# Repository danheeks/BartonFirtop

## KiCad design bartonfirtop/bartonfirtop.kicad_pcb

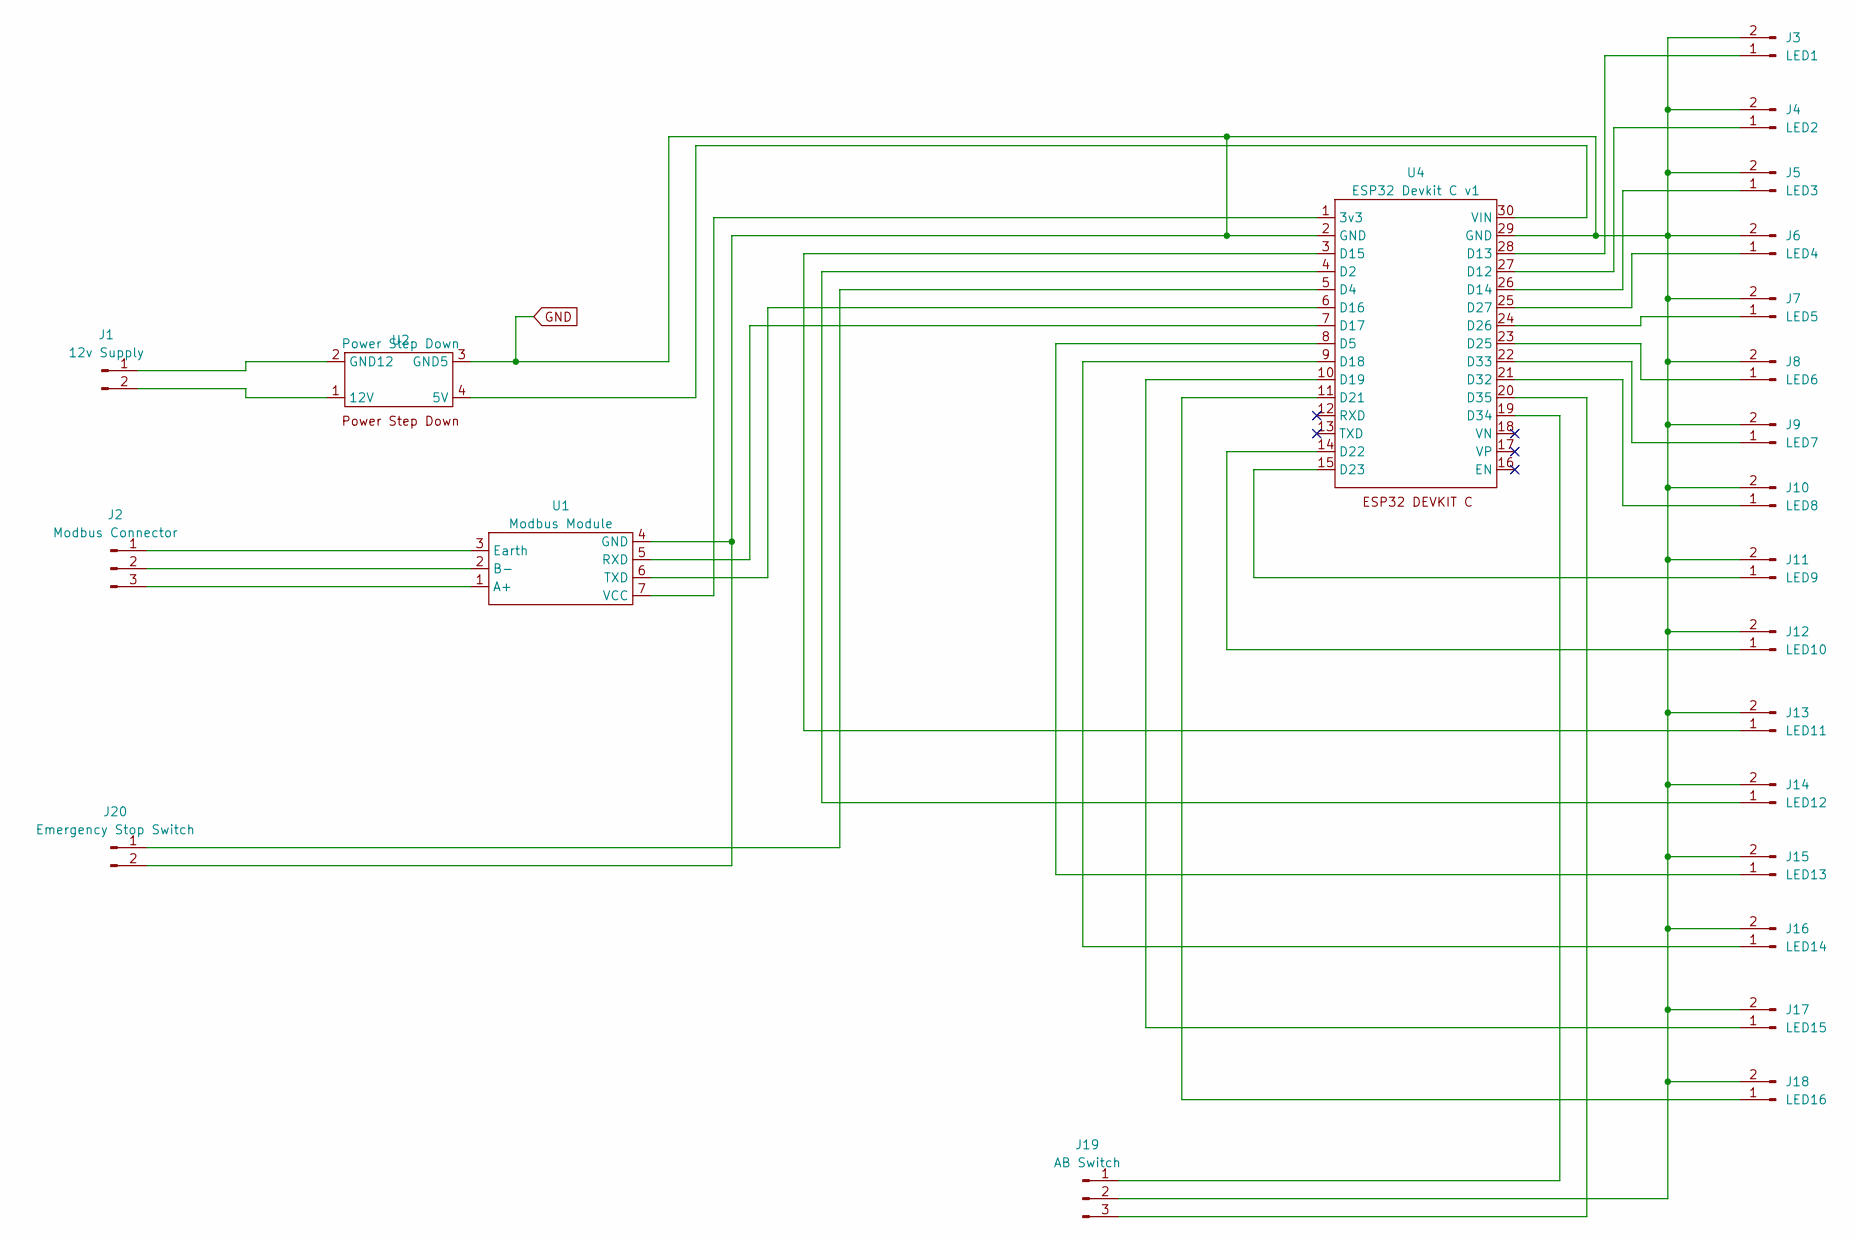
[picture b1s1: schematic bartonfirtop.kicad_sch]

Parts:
J1: 12v Supply; Molex_KK-254_AE-6410-02A_1x02_P2.54mm_Vertical
J2: Modbus Connector; Molex_KK-254_AE-6410-03A_1x03_P2.54mm_Vertical
J3: LED1; Molex_KK-254_AE-6410-02A_1x02_P2.54mm_Vertical
J4: LED2; Molex_KK-254_AE-6410-02A_1x02_P2.54mm_Vertical
J5: LED3; Molex_KK-254_AE-6410-02A_1x02_P2.54mm_Vertical
J6: LED4; Molex_KK-254_AE-6410-02A_1x02_P2.54mm_Vertical
J7: LED5; Molex_KK-254_AE-6410-02A_1x02_P2.54mm_Vertical
J8: LED6; Molex_KK-254_AE-6410-02A_1x02_P2.54mm_Vertical
J9: LED7; Molex_KK-254_AE-6410-02A_1x02_P2.54mm_Vertical
J10: LED8; Molex_KK-254_AE-6410-02A_1x02_P2.54mm_Vertical
J11: LED9; Molex_KK-254_AE-6410-02A_1x02_P2.54mm_Vertical
J12: LED10; Molex_KK-254_AE-6410-02A_1x02_P2.54mm_Vertical
J13: LED11; Molex_KK-254_AE-6410-02A_1x02_P2.54mm_Vertical
J14: LED12; Molex_KK-254_AE-6410-02A_1x02_P2.54mm_Vertical
J15: LED13; Molex_KK-254_AE-6410-02A_1x02_P2.54mm_Vertical
J16: LED14; Molex_KK-254_AE-6410-02A_1x02_P2.54mm_Vertical
J17: LED15; Molex_KK-254_AE-6410-02A_1x02_P2.54mm_Vertical
J18: LED16; Molex_KK-254_AE-6410-02A_1x02_P2.54mm_Vertical
J19: AB Switch; Molex_KK-254_AE-6410-03A_1x03_P2.54mm_Vertical
J20: Emergency Stop Switch; Molex_KK-254_AE-6410-02A_1x02_P2.54mm_Vertical
U1: Modbus Module
U2: Power Step Down; Step Down Buck Converter 24V - 5V
U4: ESP32 Devkit C v1; MODULE_ESP32_DEVKIT_V1

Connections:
GND: J3.2, J4.2, J5.2, J6.2, J7.2, J8.2, J9.2, J10.2, J11.2, J12.2, J13.2, J14.2, J15.2, J16.2, J17.2, J18.2, J19.2, J20.2, U1.4 (GND), U2.3 (GND5), U4.2 (GND), U4.29 (GND)
unnamed: J1.1, U2.2 (GND12)
unnamed: J1.2, U2.1 (12V)
unnamed: J2.1, U1.3 (Earth)
unnamed: J2.2, U1.2 (B-)
unnamed: J2.3, U1.1 (A+)
unnamed: J3.1, U4.28 (D13)
unnamed: J4.1, U4.27 (D12)
unnamed: J5.1, U4.26 (D14)
unnamed: J6.1, U4.25 (D27)
unnamed: J7.1, U4.24 (D26)
unnamed: J8.1, U4.23 (D25)
unnamed: J9.1, U4.22 (D33)
unnamed: J10.1, U4.21 (D32)
unnamed: J11.1, U4.15 (D23)
unnamed: J12.1, U4.14 (D22)
unnamed: J13.1, U4.3 (D15)
unnamed: J14.1, U4.4 (D2)
unnamed: J15.1, U4.8 (D5)
unnamed: J16.1, U4.9 (D18)
unnamed: J17.1, U4.10 (D19)
unnamed: J18.1, U4.11 (D21)
unnamed: J19.1, U4.19 (D34)
unnamed: J19.3, U4.20 (D35)
unnamed: J20.1, U4.5 (D4)
unnamed: U1.5 (RXD), U4.7 (D17)
unnamed: U1.6 (TXD), U4.6 (D16)
unnamed: U1.7 (VCC), U4.1 (3v3)
unnamed: U2.4 (5V), U4.30 (VIN)

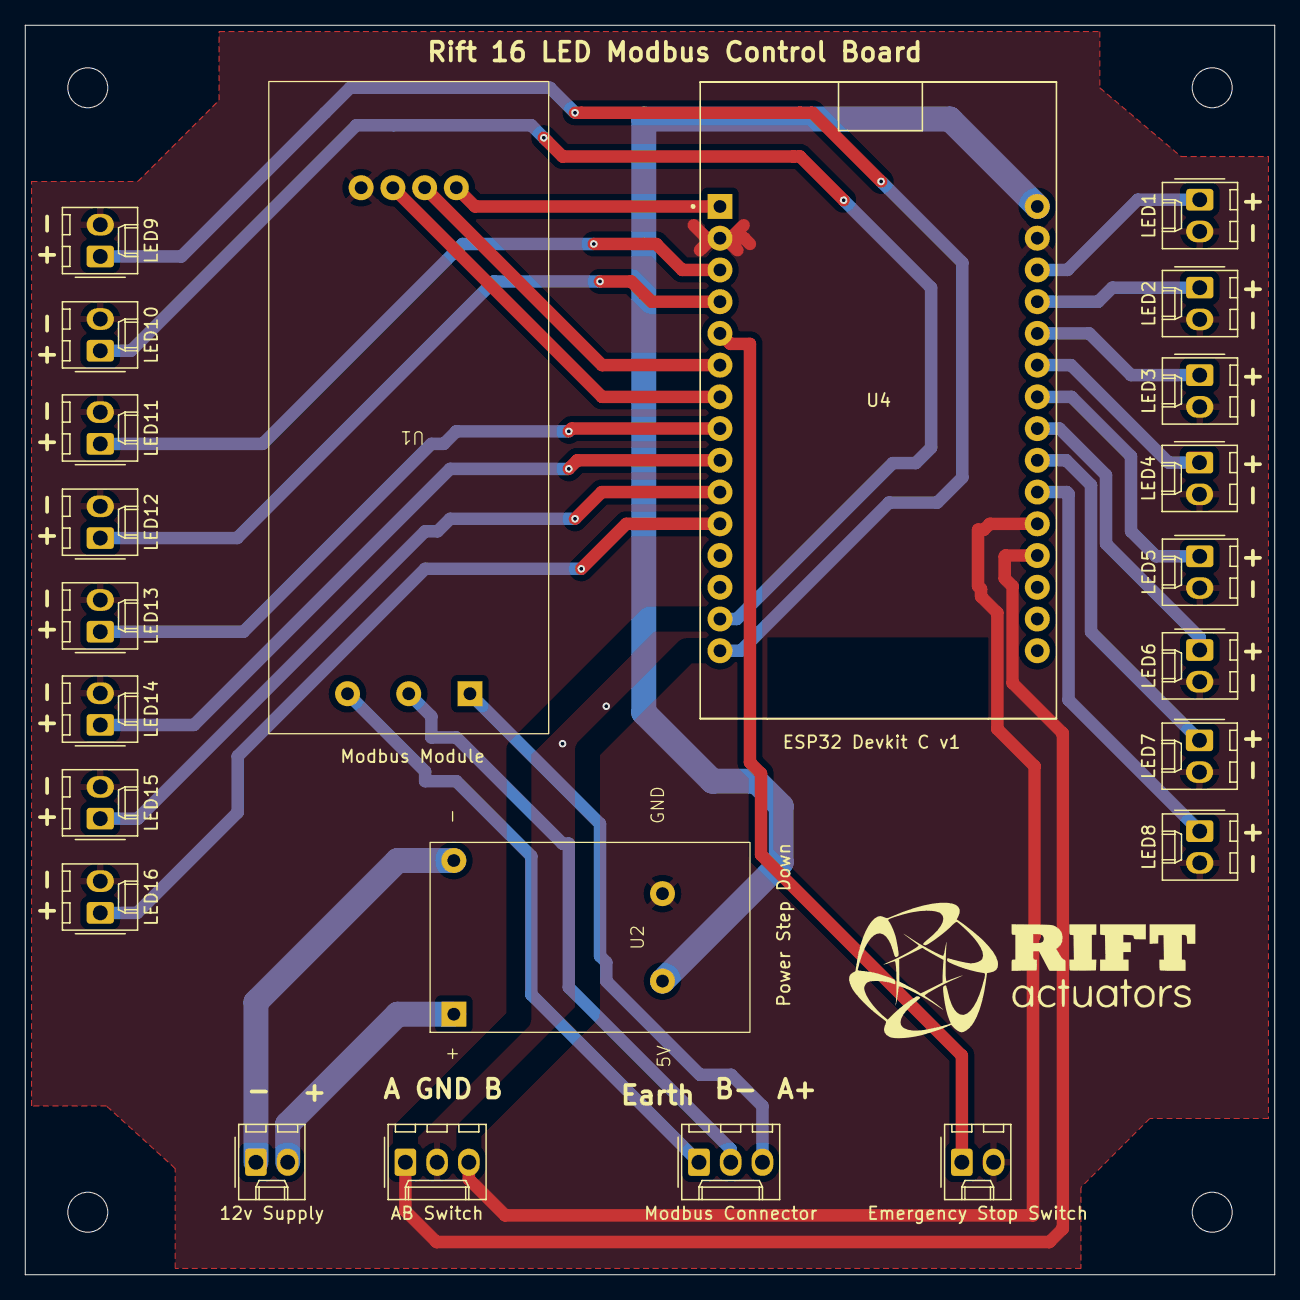
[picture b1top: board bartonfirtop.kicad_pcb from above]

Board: 2 copper layers, 100.0 x 100.0 mm, 23 parts (0 on the bottom side), 29 nets.

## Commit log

2025-01-24 work on ESP32 Barton Firtop web page app
2025-01-25 open buttons messages received by ESP32
2025-01-26 added a page with sidebar, with 2 sub-pages
2025-01-28 Getting thing centred
2025-01-28 work on schematic for board and on Arduino code
2025-01-28 I got my phone to control the actuator via ESP32 running web page
2025-01-29 added LED connectors
2025-01-30 added switches and more LEDs
2025-02-01 ordered 5 boards
2025-02-03 added Further details.docx
2025-03-07 I had + and - the wrong way for power connector
2025-03-07 work on Test Cycles
2025-03-17 Making a test cycles web page, for setting the faster RAM on test
2025-03-17 adding the 3D model for the ESP32
2025-03-17 moving the left column text to the left, deleted control.html - work is just on index.html now
2025-03-18 testing 16 LEDs on the control board
2025-03-18 I removed old arduino project to reduce confusion
2025-03-20 I split control_panel.ino and test_cycles.ino into two separate projects
2025-03-20 OK. I have all the basics working; Modbus, Wifi with web page, LEDs, SPIFFS. :) So now to get it to do a sequence that we want.
2025-03-20 Great! I have got LEDs lighting on the web page, the same as on the real control panel
2025-03-25 latest work
2025-03-25 I got a sequence working
2025-03-28 removed a while(1)
2025-05-20 schematic change
2025-05-26 coded the latest sequences and web page modifications. Still working on debugging it.
2025-05-26 added 3 way key switch
2025-05-27 added logo to repo
2025-06-10 added "Front Panel2.svg"
2025-06-13 I have got the Barton Firtop control panel working ready for visit on Monday ( 16th June 2025 )
2025-06-24 I replaced the A and B buttons on the app with a 3 position slider. You can now switch the physical AB button quickly and it still works ok. When the actuator hits a torque limit, the system fault fl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
2025-08-05 I added Rotate Clockwise and Rotate Anticlockwise to the Settings page
